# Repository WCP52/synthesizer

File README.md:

AD9958-based synthesizer board
==============================

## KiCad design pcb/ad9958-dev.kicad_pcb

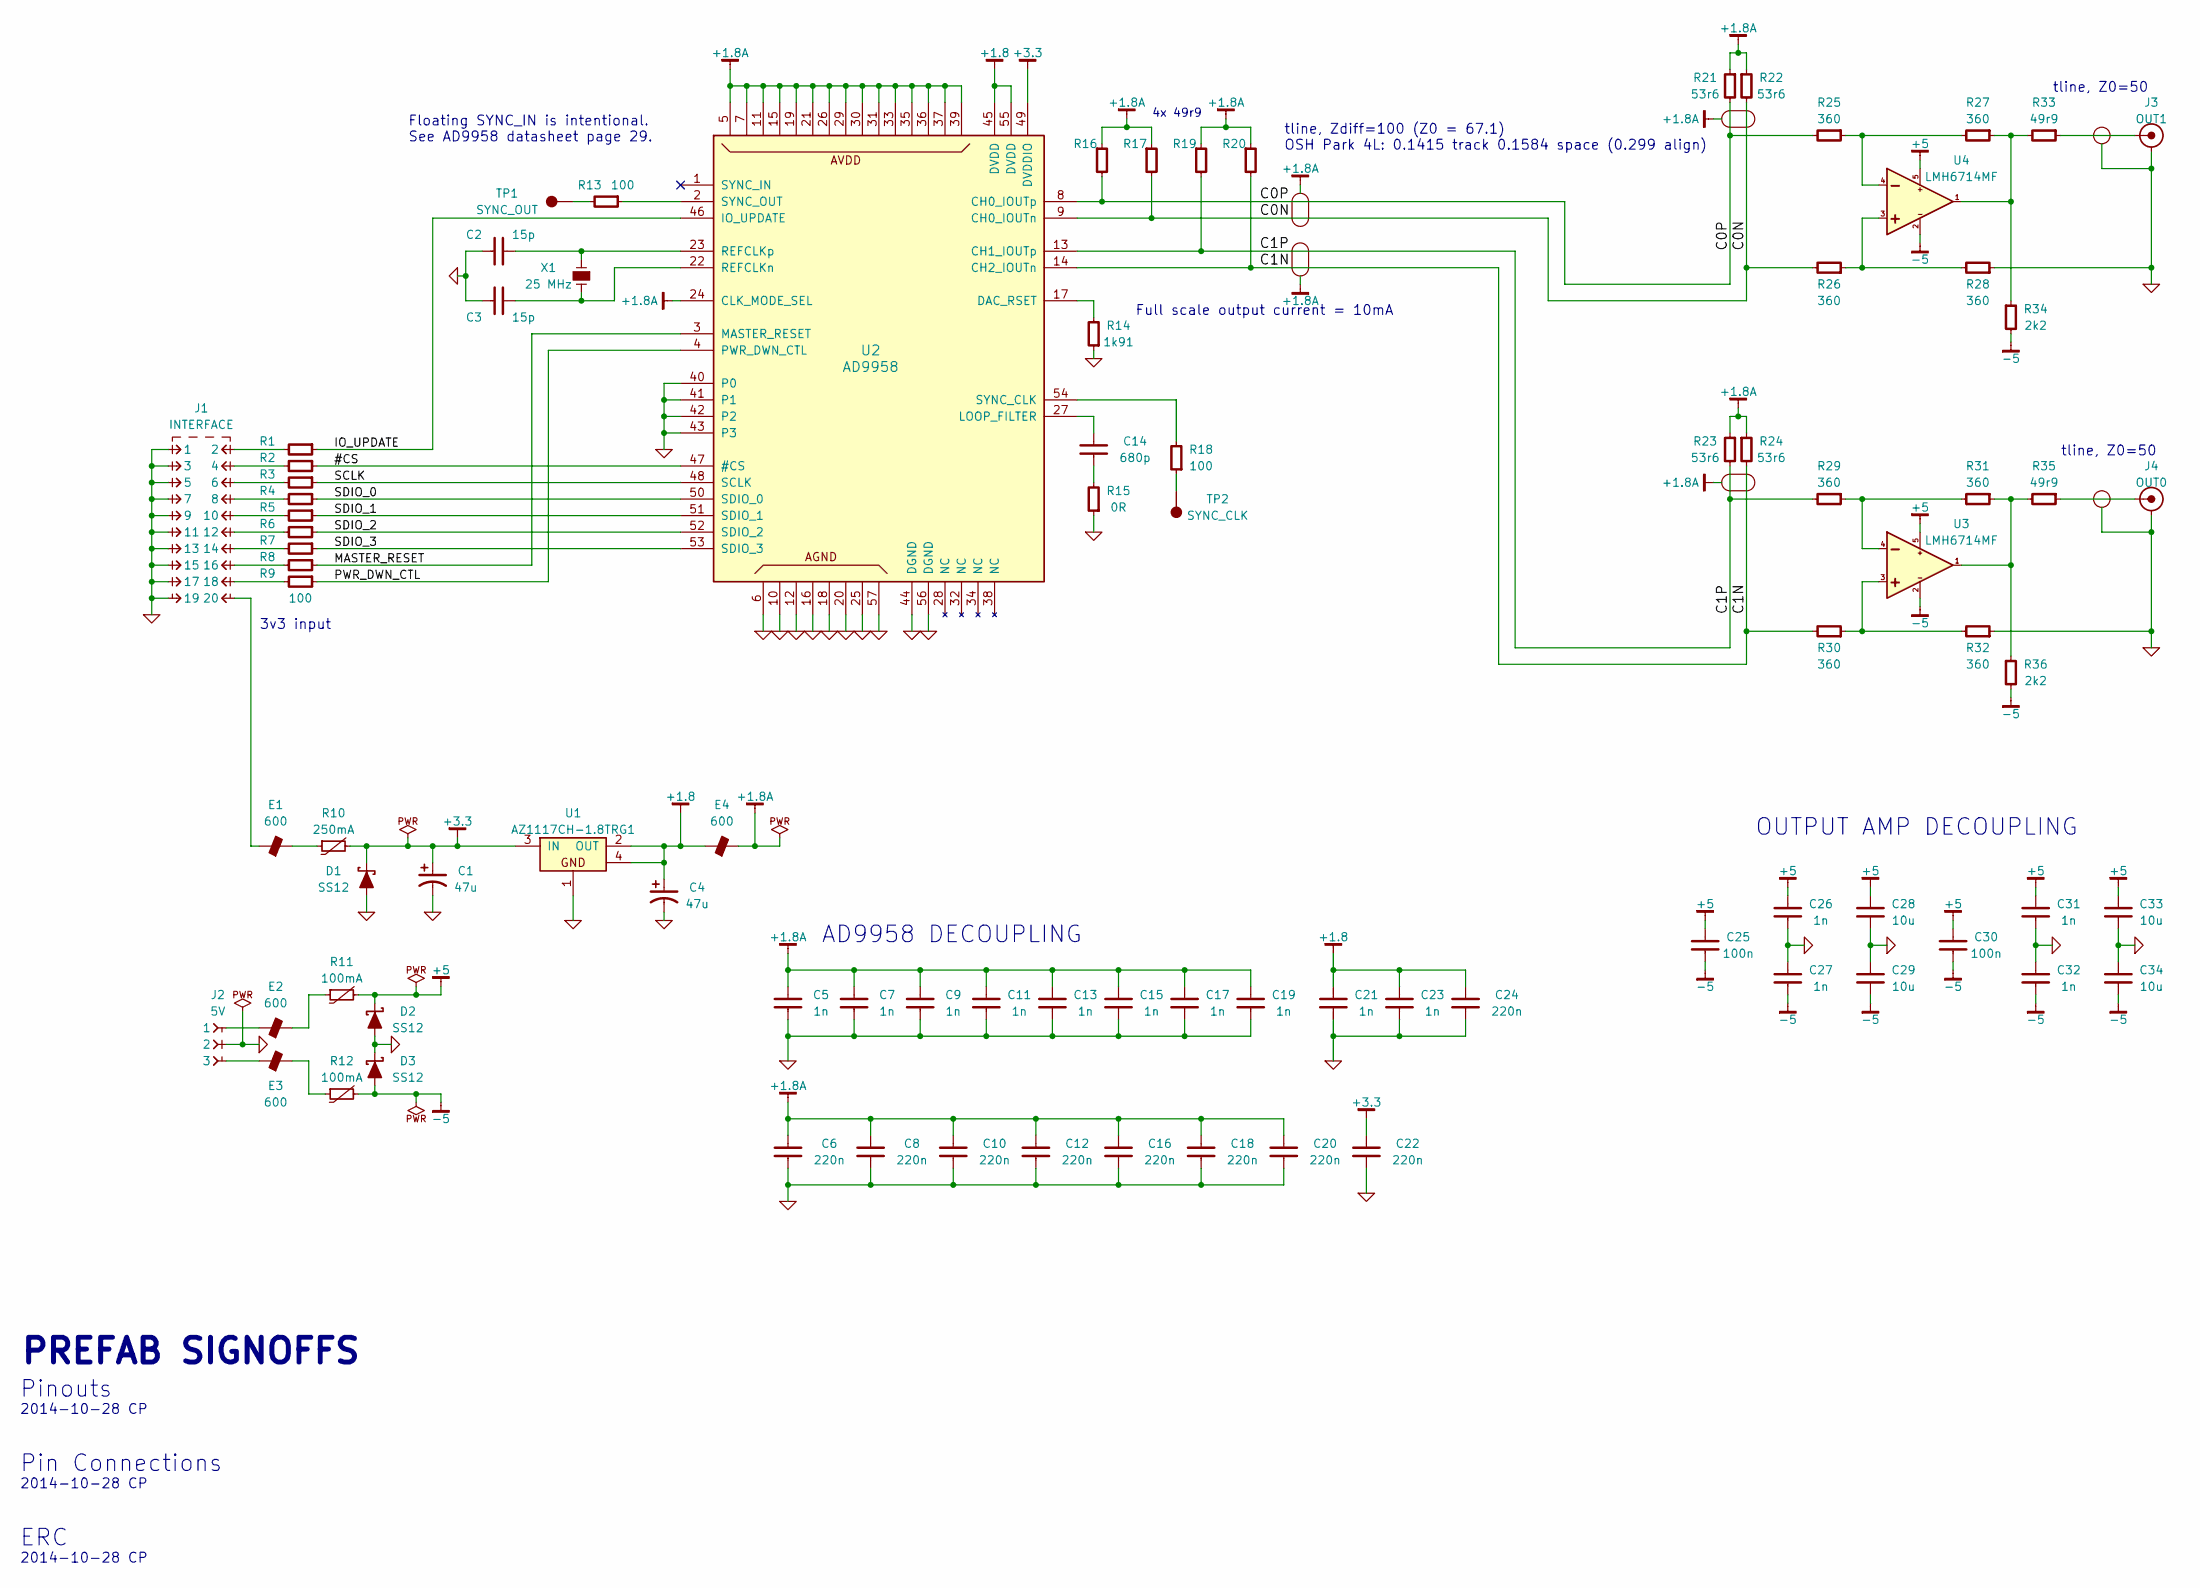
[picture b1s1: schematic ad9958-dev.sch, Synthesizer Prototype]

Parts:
C1, C4: 47u; C-ALUM-6.3mm
C2, C3: 15p; CAPC1005X55
C5, C7, C9, C11, C13, C15, C17, C19, C21, C23, C26, C27, C31, C32: 1n; CAPC1005X55
C6, C8, C10, C12, C16, C18, C20, C22, C24: 220n; CAPC2012X70
C14: 680p; CAPC1005X55
C25, C30: 100n; CAPC1005X55
C28, C29, C33, C34: 10u; CAPC2012X70
D1, D2, D3: SS12; DIOM5326X292
E1, E2, E3, E4: 600; INDC1005X60
J1: INTERFACE; CONN_20-DIL
J2: 5V; CONN_3-SIL
J3: OUT1; CONN-2_CONSMA001-SMD-G
J4: OUT0; CONN-2_CONSMA001-SMD-G
R1, R2, R3, R4, R5, R6, R7, R8, R9, R13, R18: 100; RESC1005X40
R10: 250mA; RESC3216X60
R11, R12: 100mA; RESC3216X60
R14: 1k91; RESC1005X40
R15: 0R; RESC1005X40
R16, R17, R19, R20, R33, R35: 49r9; RESC1005X40
R21, R22, R23, R24: 53r6; RESC1005X40
R25, R26, R27, R28, R29, R30, R31, R32: 360; RESC1005X40
R34, R36: 2k2; RESC1005X40
TP1: SYNC_OUT; TEST_SMD
TP2: SYNC_CLK; TEST_SMD
U1: AZ1117CH-1.8TRG1; SOT-223
U2: AD9958; LFCSP_VQ_56_ADI
U3, U4: LMH6714MF; SOT-23-5
X1: 25 MHz; XTAL1200X480X460

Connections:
+1.8: C4.1, C21.1, C23.1, C24.1, E4.2, U1.2 (OUT), U1.4, U2.45 (DVDD), U2.55 (DVDD)
/#CS: R2.1, U2.47 (#CS)
/C0N: R17.2, R22.2, R26.2, U2.9 (CH0_IOUTn)
/C0P: R16.2, R21.2, R25.2, U2.8 (CH0_IOUTp)
/C1N: R20.2, R24.2, R30.2, U2.14 (CH2_IOUTn)
/C1P: R19.2, R23.2, R29.2, U2.13 (CH1_IOUTp)
/IO_UPDATE: R1.1, U2.46 (IO_UPDATE)
/MASTER_RESET: R8.1, U2.3 (MASTER_RESET)
/PWR_DWN_CTL: R9.1, U2.4 (PWR_DWN_CTL)
/SCLK: R3.1, U2.48 (SCLK)
/SDIO_0: R4.1, U2.50 (SDIO_0)
/SDIO_1: R5.1, U2.51 (SDIO_1)
/SDIO_2: R6.1, U2.52 (SDIO_2)
/SDIO_3: R7.1, U2.53 (SDIO_3)
unnamed: C2.1, U2.23 (REFCLKp), X1.1
unnamed: C3.1, U2.22 (REFCLKn), X1.2
unnamed: C14.1, U2.27 (LOOP_FILTER)
unnamed: C14.2, R15.2
unnamed: E1.1, R10.1
unnamed: E1.2, J1.20
unnamed: E2.1, R11.1
unnamed: E2.2, J2.1
unnamed: E3.1, R12.1
unnamed: E3.2, J2.3
unnamed: J1.2, R1.2
unnamed: J1.4, R2.2
unnamed: J1.6, R3.2
unnamed: J1.8, R4.2
unnamed: J1.10, R5.2
unnamed: J1.12, R6.2
unnamed: J1.14, R7.2
unnamed: J1.16, R8.2
unnamed: J1.18, R9.2
unnamed: J3.1, R33.1
unnamed: J4.1, R35.1
unnamed: R13.1, U2.2 (SYNC_OUT)
unnamed: R13.2, TP1.1
unnamed: R14.2, U2.17 (DAC_RSET)
unnamed: R18.1, TP2.1
unnamed: R18.2, U2.54 (SYNC_CLK)
unnamed: R25.1, R27.2, U4.4 (IN-)
unnamed: R26.1, R28.2, U4.3 (IN+)
unnamed: R27.1, R33.2, R34.1, U4.1 (OUT)
unnamed: R29.1, R31.2, U3.4 (IN-)
unnamed: R30.1, R32.2, U3.3 (IN+)
unnamed: R31.1, R35.2, R36.1, U3.1 (OUT)

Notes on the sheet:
Full scale output current = 10mA
4x 49r9
tline, Zdiff=100 (Z0 = 67.1) OSH Park 4L: 0.1415 track 0.1584 space (0.299 align)
tline, Z0=50
AD9958 DECOUPLING
OUTPUT AMP DECOUPLING
3v3 input
Floating SYNC_IN is intentional. See AD9958 datasheet page 29.
PREFAB SIGNOFFS
Pinouts
2014-10-28 CP
Pin Connections
ERC

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
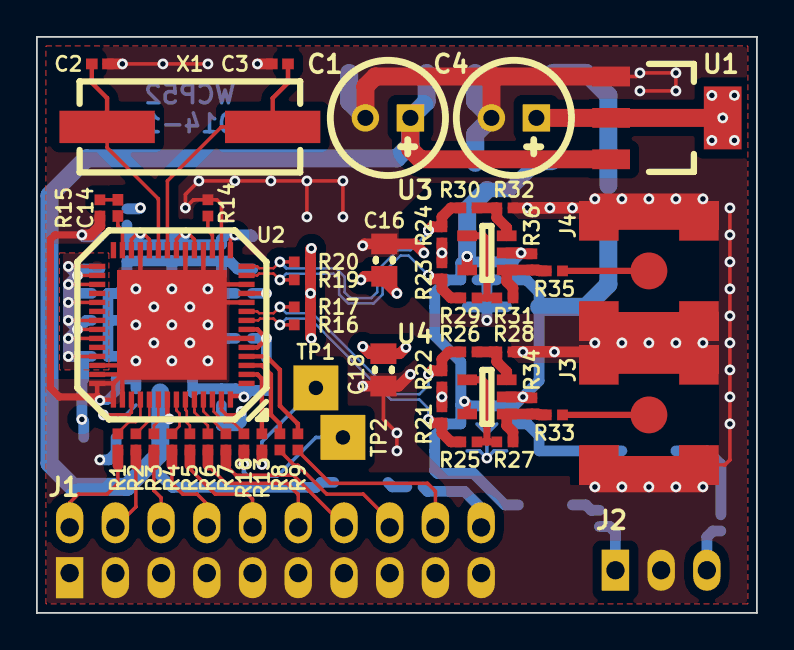
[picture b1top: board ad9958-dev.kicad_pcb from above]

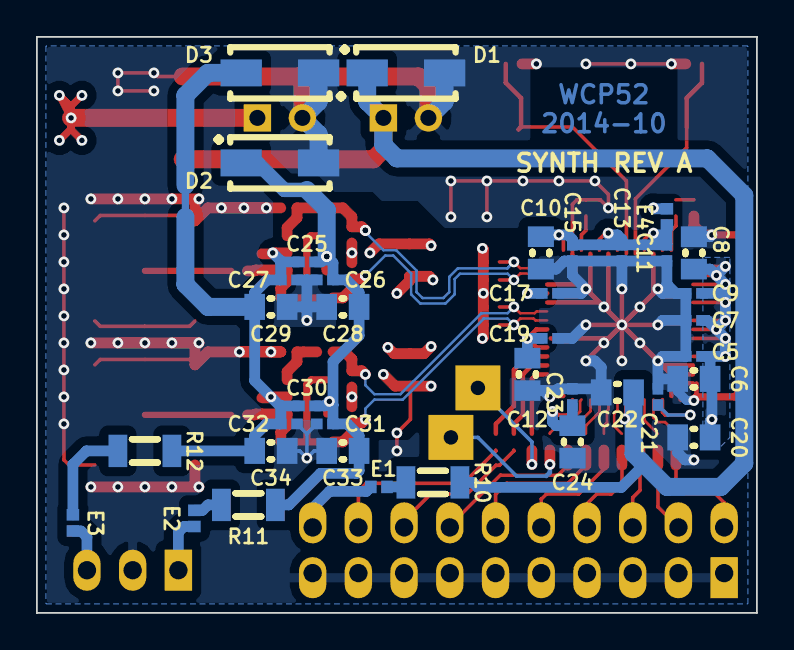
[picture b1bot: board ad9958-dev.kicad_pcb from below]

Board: 4 copper layers, 40.0 x 32.0 mm, 88 parts (37 on the bottom side), 51 nets.

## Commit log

2014-10-25 Put in very early schematic.
2014-10-25 More schematic work - should be ready for layout
2014-10-26 PCB almost done
2014-10-27 Updated AD9958 footprint.
    Still have to re-route a couple signals
2014-10-28 Added power protection, touched up PCB
2014-10-28 Few part value changes
    Added voltage to LDO
    Changed 10nF to 1nF caps - eliminated BOM item
2014-10-28 PCB touchups
2014-10-28 Schematic touchups
2014-10-28 PCB fixes
2014-10-28 Added Gerber processing and rendering
2014-10-28 Reannotated components
2014-10-28 Added small renders
2014-10-28 Prefab signoffs - CP
2014-10-28 Added schematic render
2014-10-29 Adjusted diff pair routing
    Minor PCB appearance tweak
2014-10-29 Added missing SPICE model
2014-10-29 Removed unnecessary imports from SPICE sim
2014-10-29 Tidied up simulation schematic
2014-10-30 Re-exported PCB
2014-10-30 Gerber postprocessing
2014-10-30 Gerber export
2014-11-11 Adjusted postprocessing scripts - more generic
2014-11-11 Amended postprocessing script - PDF size
2014-11-27 Added testing waveforms
2014-11-27 Added 'steps' small version
2014-11-29 Updated schematic render
